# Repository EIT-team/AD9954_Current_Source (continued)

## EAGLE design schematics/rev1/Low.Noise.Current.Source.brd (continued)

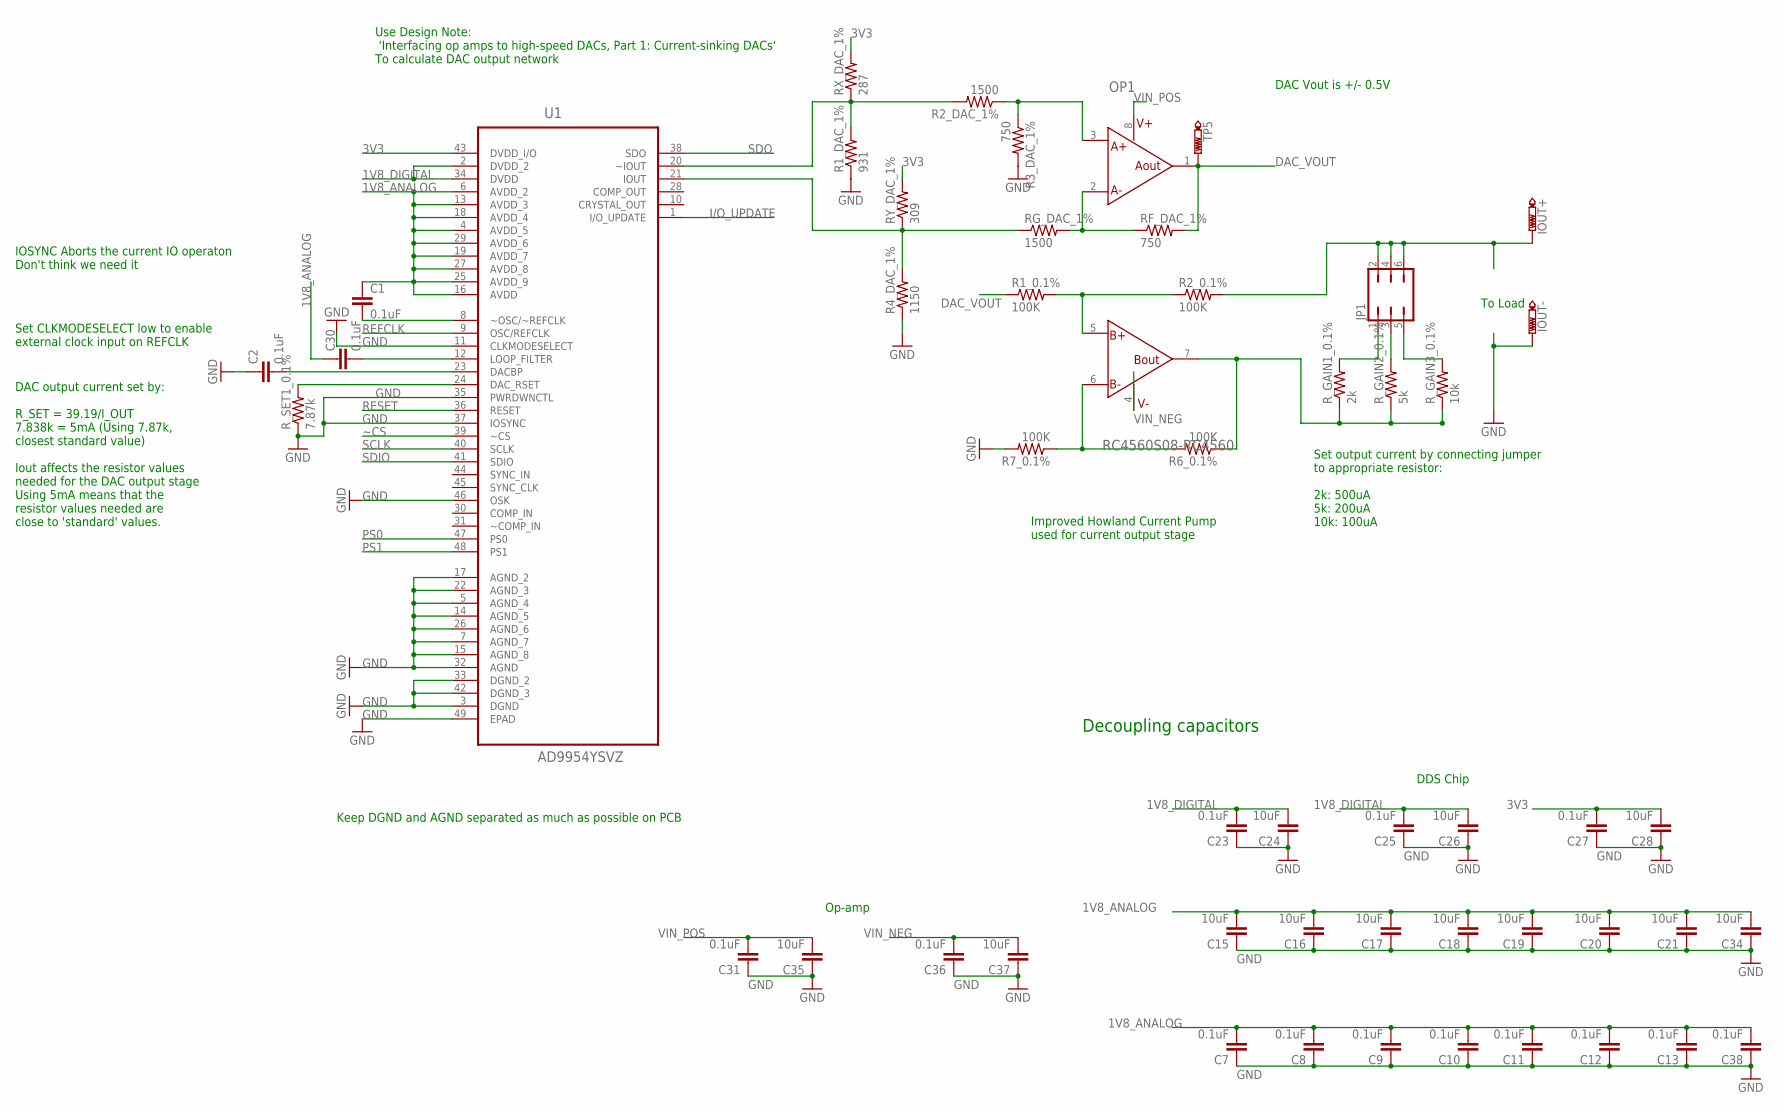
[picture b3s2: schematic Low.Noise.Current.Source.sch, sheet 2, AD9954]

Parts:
C1, C2, C7, C8, C9, C10, C11, C12, C13, C23, C25, C27, C30, C31, C36, C38: 0.1uF; C0603
C15, C16, C17, C18, C19, C20, C21, C24, C26, C28, C34, C35, C37: 10uF; C0603
IOUT+: PTR1PAD1-13; P1-13
IOUT-: PTR1PAD1-13; P1-13
JP1: JP3Q
OP1: RC4560S08-RC4560; SO8
R1_0.1%, R2_0.1%, R6_0.1%, R7_0.1%: 100K; R0805
R1_DAC_1%: 931; R0805
R2_DAC_1%: 1500; R0805
R3_DAC_1%: 750; R0805
R4_DAC_1%: 1150; R0805
RF_DAC_1%: 750; R0805
RG_DAC_1%: 1500; R0805
RX_DAC_1%: 287; R0805
RY_DAC_1%: 309; R0805
R_GAIN1_0.1%: 2k; R0805
R_GAIN2_0.1%: 5k; R0805
R_GAIN3_0.1%: 10k; R0805
R_SET1_0.1%: 7.87k; R0805
TP5: PTR1PAD1-13; P1-13
U1: AD9954YSVZ; QFP50P900X900X120-49N

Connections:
1V8_ANALOG: C1.1, C7.2, C8.2, C9.2, C10.2, C11.2, C12.2, C13.2, C15.2, C16.2, C17.2, C18.2, C19.2, C20.2, C21.2, C30.1, C34.2, C38.2, U1.4 (AVDD_5), U1.6 (AVDD_2), U1.13 (AVDD_3), U1.16 (AVDD), U1.18 (AVDD_4), U1.19 (AVDD_7), U1.25 (AVDD_9), U1.27 (AVDD_8), U1.29 (AVDD_6); also elsewhere on the board
1V8_DIGITAL: C23.2, C24.2, C25.2, C26.2, U1.2 (DVDD_2), U1.34 (DVDD); also elsewhere on the board
3V3: C27.2, C28.2, RX_DAC_1%.2, RY_DAC_1%.2, U1.43 (DVDD_I/O); also elsewhere on the board
DAC_VOUT: OP1.1 (OUTA), R1_0.1%.1, RF_DAC_1%.2, TP5.TP
GND: C2.1, C7.1, C8.1, C9.1, C10.1, C11.1, C12.1, C13.1, C15.1, C16.1, C17.1, C18.1, C19.1, C20.1, C21.1, C23.1, C24.1, C25.1, C26.1, C27.1, C28.1, C31.1, C34.1, C35.1, C36.1, C37.1, C38.1, IOUT-.TP, R1_DAC_1%.1, R3_DAC_1%.2, R4_DAC_1%.1, R7_0.1%.2, R_SET1_0.1%.1, U1.3 (DGND), U1.5 (AGND_4), U1.7 (AGND_7), U1.11 (CLKMODESELECT), U1.14 (AGND_5), U1.15 (AGND_8), U1.17 (AGND_2), U1.22 (AGND_3), U1.26 (AGND_6), U1.32 (AGND), U1.33 (DGND_2), U1.35 (PWRDWNCTL), U1.37 (IOSYNC), U1.42 (DGND_3), U1.46 (OSK), U1.49 (EPAD); also elsewhere on the board
I/O_UPDATE: U1.1 (I/O_UPDATE); also elsewhere on the board
IOUT: R4_DAC_1%.2, RG_DAC_1%.1, RY_DAC_1%.1, U1.21 (IOUT)
unnamed: C2.2, U1.23 (DACBP)
unnamed: C1.2, U1.8 (~OSC/~REFCLK)
unnamed: R_SET1_0.1%.2, U1.24 (DAC_RSET)
unnamed: OP1.3 (POSA), R2_DAC_1%.1, R3_DAC_1%.1
unnamed: OP1.5 (POSB), R1_0.1%.2, R2_0.1%.1
unnamed: OP1.2 (NEGA), RF_DAC_1%.1, RG_DAC_1%.2
unnamed: OP1.6 (NEGB), R6_0.1%.2, R7_0.1%.1
unnamed: OP1.7 (OUTB), R6_0.1%.1, R_GAIN1_0.1%.1, R_GAIN2_0.1%.1, R_GAIN3_0.1%.1
unnamed: C30.2, U1.12 (LOOP_FILTER)
unnamed: IOUT+.TP, JP1.2, JP1.4, JP1.6, R2_0.1%.2
unnamed: JP1.3, R_GAIN2_0.1%.2
unnamed: JP1.5, R_GAIN3_0.1%.2
unnamed: JP1.1, R_GAIN1_0.1%.2
PS0: U1.47 (PS0); also elsewhere on the board
PS1: U1.48 (PS1); also elsewhere on the board
REFCLK: U1.9 (OSC/REFCLK); also elsewhere on the board
RESET: U1.36 (RESET); also elsewhere on the board
SCLK: U1.40 (SCLK); also elsewhere on the board
SDIO: U1.41 (SDIO); also elsewhere on the board
SDO: U1.38 (SDO); also elsewhere on the board
VIN_NEG: C36.2, C37.2, OP1.4 (V-); also elsewhere on the board
VIN_POS: C31.2, C35.2, OP1.8 (V+); also elsewhere on the board
~CS: U1.39 (~CS); also elsewhere on the board
~IOUT: R1_DAC_1%.2, R2_DAC_1%.2, RX_DAC_1%.1, U1.20 (~IOUT)

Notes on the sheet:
Set CLKMODESELECT low to enable external clock input on REFCLK
DAC output current set by: R_SET = 39.19/I_OUT 7.838k = 5mA (Using 7.87k, closest standard value) Iout affects the resistor values needed for the DAC output stage Using 5mA means that the resistor values needed are close to 'standard' values.
IOSYNC Aborts the current IO operaton Don't think we need it
Decoupling capacitors
Use Design Note: 'Interfacing op amps to high-speed DACs, Part 1: Current-sinking DACs' To calculate DAC output network
Keep DGND and AGND separated as much as possible on PCB
DAC Vout is +/- 0.5V
DDS Chip
Op-amp
Set output current by connecting jumper to appropriate resistor: 2k: 500uA 5k: 200uA 10k: 100uA
To Load
Improved Howland Current Pump used for current output stage

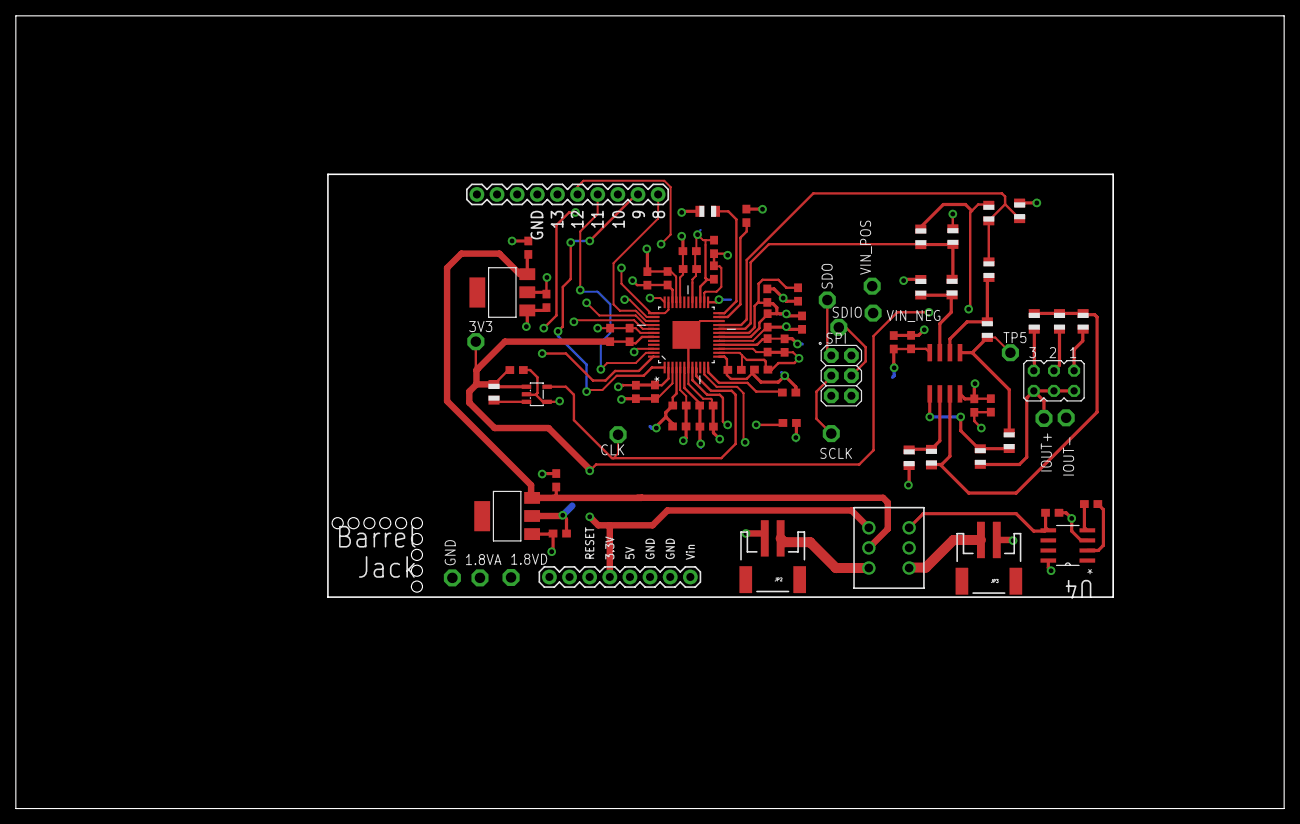
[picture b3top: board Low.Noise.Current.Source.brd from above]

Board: 4 copper layers, 160.0 x 100.0 mm, 77 parts (0 on the bottom side), 37 nets.

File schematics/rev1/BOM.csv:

"Qty";"Value";"Device";"Package";"Parts";"Description";"MF";"MPN";"OC_FARNELL";"OC_NEWARK";"PACKAGE";"SUPPLIER";"TP_SIGNAL_NAME";
"1";"";"JP3Q";"JP3Q";"JP1";"JUMPER";"";"";"";"";"";"";"";
"2";"";"M02-JST-2MM-SMT";"JST-2-SMD";"JP2, JP3";"Header 2";"";"";"";"";"";"";"";
"19";"0.1uF";"C-EUC0603";"C0603";"C1, C2, C4, C6, C7, C8, C9, C10, C11, C12, C13, C23, C25, C27, C29, C30, C31, C36, C38";"CAPACITOR, European symbol";"";"";"";"";"";"";"";
"4";"100K";"R-US_R0805";"R0805";"R1_0.1%, R2_0.1%, R6_0.1%, R7_0.1%";"RESISTOR, American symbol";"";"";"";"";"";"";"";
"2";"10k";"R-US_R0805";"R0805";"R3, R_GAIN3_0.1%";"RESISTOR, American symbol";"";"";"";"";"";"";"";
"17";"10uF";"C-EUC0603";"C0603";"C3, C5, C15, C16, C17, C18, C19, C20, C21, C24, C26, C28, C32, C33, C34, C35, C37";"CAPACITOR, European symbol";"";"";"";"";"";"";"";
"1";"1150";"R-US_R0805";"R0805";"R4_DAC_1%";"RESISTOR, American symbol";"";"";"";"";"";"";"";
"2";"1500";"R-US_R0805";"R0805";"R2_DAC_1%, RG_DAC_1%";"RESISTOR, American symbol";"";"";"";"";"";"";"";
"1";"287";"R-US_R0805";"R0805";"RX_DAC_1%";"RESISTOR, American symbol";"";"";"";"";"";"";"";
"1";"2k";"R-US_R0805";"R0805";"R_GAIN1_0.1%";"RESISTOR, American symbol";"";"";"";"";"";"";"";
"1";"309";"R-US_R0805";"R0805";"RY_DAC_1%";"RESISTOR, American symbol";"";"";"";"";"";"";"";
"1";"5k";"R-US_R0805";"R0805";"R_GAIN2_0.1%";"RESISTOR, American symbol";"";"";"";"";"";"";"";
"1";"7.838k";"R-US_R0805";"R0805";"R_SET1_0.1%";"RESISTOR, American symbol";"";"";"";"";"";"";"";
"2";"750";"R-US_R0805";"R0805";"R3_DAC_1%, RF_DAC_1%";"RESISTOR, American symbol";"";"";"";"";"";"";"";
"1";"931";"R-US_R0805";"R0805";"R1_DAC_1%";"RESISTOR, American symbol";"";"";"";"";"";"";"";
"1";"AD9954YSVZ";"AD9954YSVZ";"QFP50P900X900X120-49N";"U1";"Direct Digital Synthesizer";"";"AD9954YSVZ";"1581969";"19M8953";"TQFP-48";"ANALOG DEVICES";"";
"1";"ARDUINO_DUE";"ARDUINO_DUE";"ARDUINO_DUE";"PCB1";"Device for representing an Arduino Due board with a footprint in an EAGLE design. Created by Dave Young for Element14. More EAGLE documentation at: http://www.element14.com/community/community/knode/cadsoft_eagle";"";"";"";"";"";"";"";
"1";"LTC1044CS8PBF";"LTC1044CS8PBF";"SOIC127P600X175-8N";"U4";"Switched Capacitor Voltage Converter";"";"LTC1044CS8#PBF";"1663593";"55M8900";"SOIC-8";"Linear Technology";"";
"1";"LTC69000";"LTC69000";"SOT23-5L";"U2";"Low Power, 1kHz to 20MHz";"";"";"";"";"";"";"";
"13";"PTR1PAD1-13";"PTR1PAD1-13";"P1-13";"1.8VA, 1.8VD, 3V3, CLK, GND, IOUT+, IOUT-, SCLK, SDIO, SDO, TP5, VIN_NEG, VIN_POS";"TEST PIN";"";"";"";"";"";"";"";
"1";"RC4560S08-RC4560";"RC4560S08-RC4560";"SO8";"OP1";"RC4560 Op-Amp";"";"";"";"";"";"";"";
"2";"REG1117";"REG1117";"SOT223";"IC1, IC2";"800mA and 1A Low Dropout (LDO) Positive Regulator";"";"REG1117";"1097566";"14P6981";"";"";"";
"1";"TL42PO";"TL42PO";"TL4XPO";"S3";"TINY SWITCH ON - MOM";"";"";"";"";"";"";"";

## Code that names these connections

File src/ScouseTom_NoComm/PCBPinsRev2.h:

 /*Changed numbering so we can use the CS on the Rev1 shield but still use the indicators*/

// switch network pin definitions
const int DINp = 10;
const int DINn = 11;
const int SCLK = 12;
const int SYNC = 8;
const int RESET = 9;
const int TEST_1 = 7;
const int TEST_2 = 13;

// indicator pins
const int IND_SWITCH = 3;
const int IND_STIM = 4;
const int IND_START = 5;
const int IND_STOP = 6;
const int IND_FREQ = 16;

const int IND_EX_1= 15;
const int IND_EX_2= 14;
const int IND_EX_3= 2;

//AD9954 pins

const int SS_PIN = 17;
const int RESET_PIN = 21;
const int UPDATE_PIN = 18;
const int PS0 = 20;
const int PS1 = 19;
const int OSK = 27;


/*
//pins to turn the triggers on and off
const int TRIG_DISABLE_1 = 7;
const int TRIG_DISABLE_2 = 13; 

//interupt pins
const int INTR_PMARK = 25; // pin to decect pmark - MUST BE AT POSITION 0 OF A DUE PORT 25 is 0 on portD - check http://arduino.cc/en/Hacking/PinMappingSAM3X
const int CS_EXTRA=24; // bonus output pin on the CS side, not really used but whatever

//bonus pins
const int BONUS_1 =47;
const int BONUS_2 =49;
const int BONUS_3 =51;
const int BONUS_4 =53;

//Power Pins
const int PWR_STIM = 52;
const int PWR_SWITCH = 22;
*/

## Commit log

2013-02-08 initial commit: arduino - AD9954 DDS communication library
2013-02-26 random changes; more or less working; need to clean up some things still
2013-03-27 cleaned up some things; added register command to auto reset phase counter
2013-05-03 functioning frequency sweep code for AD9954
2013-05-03 added documentation for AD9954, removed Serail.println lines
2013-10-02 proper update for setFTW after being in linear sweep mode
2014-09-17 fixed issue in AD9954 for static const RESOLUTION
2014-09-20 Updated README
    Added semicolon to code example
2014-09-20 Re-fixed issue with AD9954 library, making RESOLUTION a private double and assigning its value in the class constructor.
    Should be stable now. Foolish choices :)
2015-01-15 Added .gitignore
2015-11-30 Explicitly ramp AD9954 in linearSweep function
2017-08-24 Starting to clean up code
2017-08-24 Can set frequency & turn on/off through Serial commands
2017-08-25 Added MATLAB serial programming example
2017-08-25 Added comments
2017-11-15 added simple fixed current amplitude with no serial comm
2019-01-07 Added Rev1 Schematics
2019-01-10 added reference things for AD9954
2019-01-15 Added tests for controlling Switch board and doing indicators
2019-01-30 added ref for DAC calculations and ICs used
2019-01-30 rev2 routing and layout done. still takes too much space
2019-01-30 layout and some polygons done
2019-01-30 no DRC errors
2019-02-04 board finished
2019-06-10 added smaller VDAC out calculation
2019-06-10 added spice model of DAC network
2019-06-11 Tests and Simple control for rev2 board
2019-06-13 Simple Control split into separate tabs
2019-06-13 removed vscode settings files
2019-07-11 Working version of ScouseTom control code, stim and MF working with AD9954 CS control
2019-08-19 Added contact check back in
2019-08-19 moved other arduino programs to test
2019-08-19 added example matlab usage
2019-11-06 Latest Rev2 and USB_ISO
2021-06-29 SMD soldering guides Rev2
2021-06-29 changes to DAC resistor network
2021-06-30 Added matlab code so its all in one repo
2021-07-05 Added shunting 12 sinks together
